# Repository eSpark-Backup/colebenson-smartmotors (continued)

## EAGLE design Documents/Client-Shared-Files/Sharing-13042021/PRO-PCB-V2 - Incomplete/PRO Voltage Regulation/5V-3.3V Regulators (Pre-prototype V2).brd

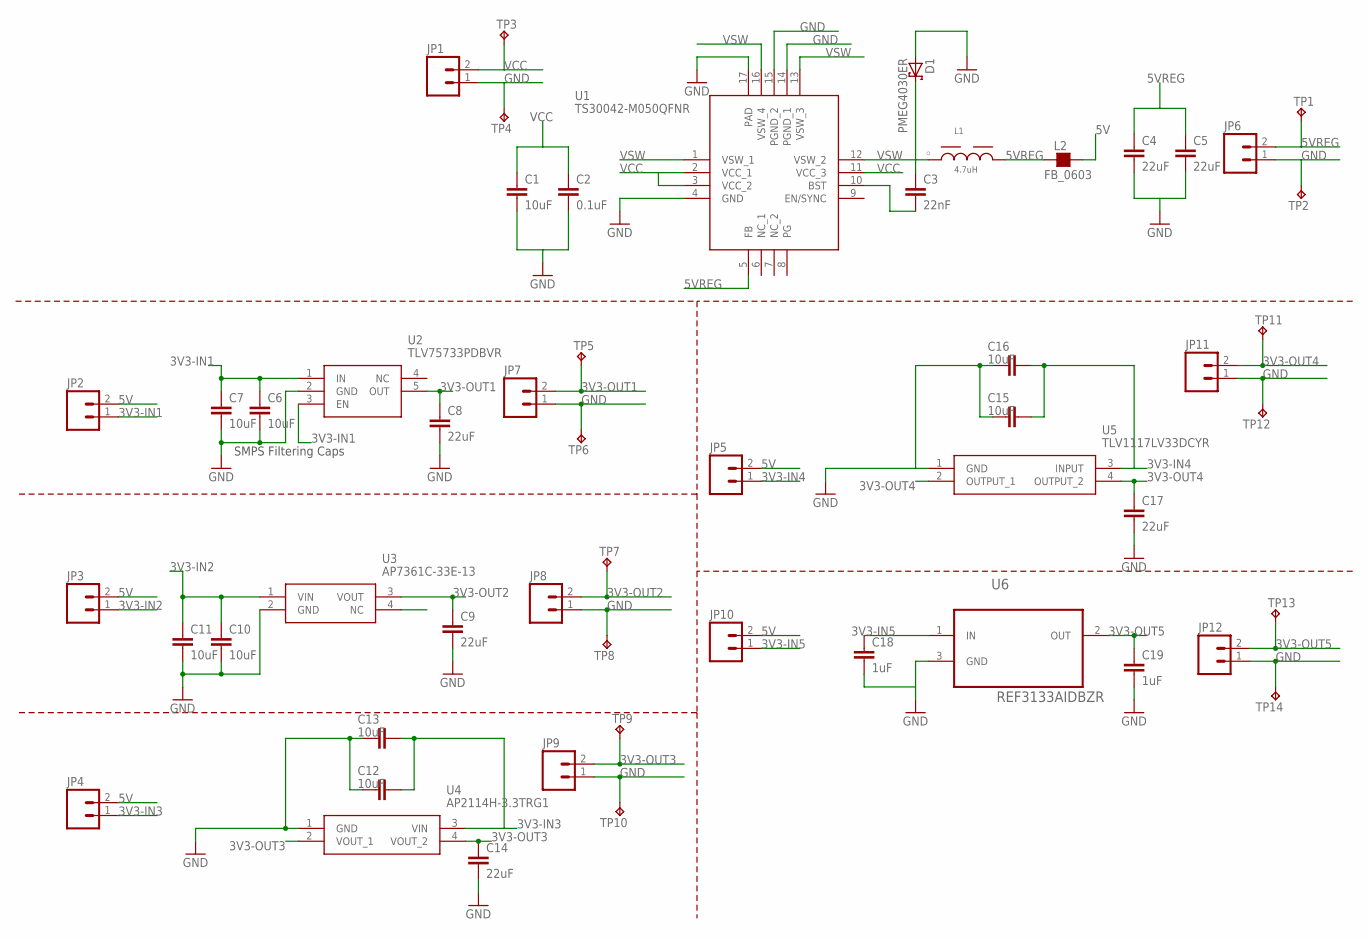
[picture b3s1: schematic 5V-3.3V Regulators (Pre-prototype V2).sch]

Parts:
C1: 10uF; 1206
C2: 0.1uF; 0603-CAP
C3: 22nF; 0402-CAP
C4, C5, C8, C9, C14, C17: 22uF; 0805
C6, C7, C10, C11, C12, C13, C15, C16: 10uF; 0805
C18, C19: 1uF; 0805
D1: PMEG4030ER; SOD123W
JP1, JP2, JP3, JP4, JP5, JP6, JP7, JP8, JP9, JP10, JP11, JP12: M02PTH; 1X02
L1: 4.7uH; WE-PD2_5848/5820
L2: FB_0603; L0603
TP1, TP2, TP3, TP4, TP5, TP6, TP7, TP8, TP9, TP10, TP11, TP12, TP13, TP14: TP-040
U1: TS30042-M050QFNR; QFN16
U2: TLV75733PDBVR; SOT95P280X145-5N
U3: AP7361C-33E-13; SOT230P700X165-4N
U4: AP2114H-3.3TRG1; SOT230P700X180-4N
U5: TLV1117LV33DCYR; SOT230P700X180-4N
U6: REF3133AIDBZR; SOT95P237X112-3N

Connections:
3V3-IN1: C6.1, C7.1, JP2.1, U2.1 (IN), U2.3 (EN)
3V3-IN2: C10.1, C11.1, JP3.1, U3.1 (VIN)
3V3-IN3: C12.1, C13.1, JP4.1, U4.3 (VIN)
3V3-IN4: C15.1, C16.1, JP5.1, U5.3 (INPUT)
3V3-IN5: C18.1, JP10.1, U6.1 (IN)
3V3-OUT1: C8.1, JP7.2, TP5.1, U2.5 (OUT)
3V3-OUT2: C9.1, JP8.2, TP7.1, U3.3 (VOUT)
3V3-OUT3: C14.1, JP9.2, TP9.1, U4.2 (VOUT_1), U4.4 (VOUT_2)
3V3-OUT4: C17.1, JP11.2, TP11.1, U5.2 (OUTPUT_1), U5.4 (OUTPUT_2)
3V3-OUT5: C19.1, JP12.2, TP13.1, U6.2 (OUT)
5V: JP2.2, JP3.2, JP4.2, JP5.2, JP10.2, L2.2
5VREG: C4.1, C5.1, JP6.2, L1.2, L2.1, TP1.1, U1.5 (FB)
GND: C1.2, C2.2, C4.2, C5.2, C6.2, C7.2, C8.2, C9.2, C10.2, C11.2, C12.2, C13.2, C14.2, C15.2, C16.2, C17.2, C18.2, C19.2, D1.2 (A), JP1.1, JP6.1, JP7.1, JP8.1, JP9.1, JP11.1, JP12.1, TP2.1, TP4.1, TP6.1, TP8.1, TP10.1, TP12.1, TP14.1, U1.4 (GND), U1.14 (PGND_1), U1.15 (PGND_2), U1.17 (PAD), U2.2 (GND), U3.2 (GND), U4.1 (GND), U5.1 (GND), U6.3 (GND)
unnamed: C3.2, U1.10 (BST)
VCC: C1.1, C2.1, JP1.2, TP3.1, U1.2 (VCC_1), U1.3 (VCC_2), U1.11 (VCC_3)
VSW: C3.1, D1.1 (K), L1.1, U1.1 (VSW_1), U1.12 (VSW_2), U1.13 (VSW_3), U1.16 (VSW_4)

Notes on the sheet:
SMPS Filtering Caps

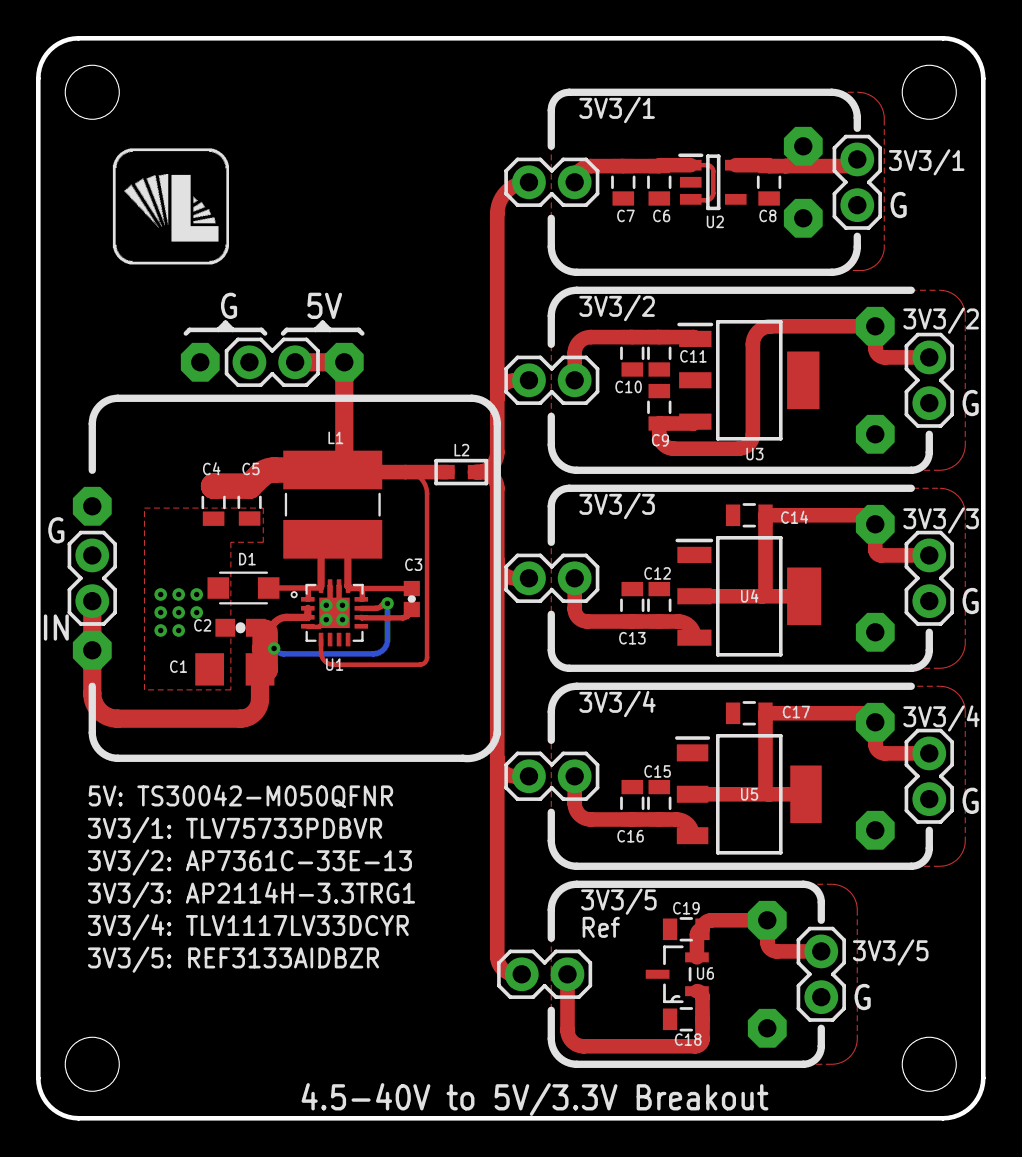
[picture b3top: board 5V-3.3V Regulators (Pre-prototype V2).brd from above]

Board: 2 copper layers, 52.5 x 60.0 mm, 54 parts (0 on the bottom side), 16 nets.

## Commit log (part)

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2022-01-08 All changes in #35. PCB updated.
2022-01-10 Routing in Top PCB.
2022-01-28 Power section updated #39
2022-01-29 #40 Completed
2022-01-29 Power section changed in top board #41. PDF creataed.
2022-01-31 Power section completed #41. Fresh PDF generated.
2022-02-01 3.3V LED added. Fresh PDF generated. Refer to #45 for details
    All required connections updated.
2022-02-01 22uH inductor replaced in Power section #44
2022-02-02 #42 Completed
2022-02-05 Encoder Noise Charts uploaded
2022-02-07 Ferrite beads added in schematic and library issue #48
2022-02-10 #51 Completed
2022-02-11 #50 and #52 updated.
2022-02-12 issue #50 and #52 completed
2022-02-14 #54 Completed
2022-02-15 #54 Error removed
2022-02-15 #55 Completed
2022-02-16 library compiled to avoid conflict while merging library addition branch,
2022-02-17 Regulator outputs updated, isolated coverter completed, gnds separated in all sheets.
2022-02-17 #58 Completed @UroojNav Inductor b add kr dia ha Acc to #55
2022-02-18 Changes done acc #47
2022-02-21 Parts Placement acc: #60
2022-02-22 GNDs isolated, signals corrected and errors removed #47
2022-02-22 Generated step files of Top board
2022-02-24 Corrections of isolated signals #58 #47
2022-02-24 Replaced switches with headers Issue #64
2022-02-24 PCB Routing completed #62 (errors and Warning remains)
2022-02-26 Minor changes in PCB. Refer to #70
2022-02-26 Changes done acc: #71
2022-02-28 Changes done acc #74
2022-02-28 Issue #75 Pending
2022-02-28 Minor changes in SM_Bottom_PCB after review. Refer to #73 PCB Designing -Review of routing of SM_Bottom_PCB #73
2022-03-03 Changes done according to #77
2022-03-03 Design PDFs generated (both boards)
2022-03-05 History and Preview folders deleted after Review of Both PCB's.
2022-03-07 Deliverables generated(Pick and place file and step file remaining
2022-03-11 Top Board Schematic Review (Pending)
2022-03-14 MAX14850ASE+ lib corrected. #81 resolved.
2022-03-14 #80 resolved.
2022-03-15 J1 replaced #83 PCB updated.
2022-03-16 #31 Completed.
2022-03-16 Revert "#31 Completed."
    This reverts commit dc2824ba49c5024c31e5d71a851132d0e0f728fc.
2022-03-18 #89 Completed
2022-03-21 Changes done acc #91 and Fresh deliverables generated #85
2022-03-22 Changes done acc #92(incompleted)
2022-03-25 #92 Completed
2022-03-28 #95 Completed
2022-03-29 Alternate added for ESD diodes and X2 #95
2022-03-31 PCB Updated acc to #98 and deliverables generated (#85) for top board
2022-04-01 Top Sheet Reviewed
2022-04-01 Revert "Schematic review"
2022-04-01 #104 Completed
2022-04-02 U4 changed in bottom board. #103
2022-04-06 #105 Completed
2022-04-06 Fresh Deliverables generated for bottom board and PDF generated for both board #106
2022-04-06 18ebcbc7 - Fresh DXF, DWG, 3D PDF and Step file for both Top and Bottom Boards generated.file.
2022-04-07 #107 Complete
2022-04-07 Mechanical Issues from client
2022-04-13 Worked completed on #109 and Fresh Deliverables generated
2022-04-27 Latest Deliverables generated for both Top and Bottom Boards.
2022-04-29 NC_Drill and Gerber Files Generated for Both both board
2022-07-19 #116 Completed
2022-07-21 branch info updated in readme of main
2022-07-21 modified .gitignore
2022-07-22 Word document submitted to client #121
2022-07-22 designator issue resolved #122
2022-07-22 connections corrected #125
2022-07-22 Resolved #123
2022-08-05 #128 #125 completed
2022-08-05 #130 Completed.
2022-08-05 Minor changes in Client BOM
2022-08-10 worked on #133 completed
2022-08-11 DRC Errors corrected #132 for details.
2022-08-12 BOM Economization #135
2022-08-15 @faizi968 TOP BOM Updated.
2022-08-15 BOM Economization (Complete) #135
2022-08-17 30-12V Buck Converter Design changes
2022-08-18 BOM and schematic changes #135
2022-08-19 #137 Updated Library,
2022-08-19 Library - Ref BOM - Schematic Changes #135 #137
2022-08-20 Top board BOM review (in progress)
2022-08-21 220nF capacitor part number merged
2022-08-21 Top Board BOM finalized
2022-08-21 Minor BOM formatting
2022-08-21 Bottom Board BOM Economization #135 (in progress)
2022-08-21 File name edited for BOMs (Top and Bottom)
2022-08-24 Routing completed of top board #138
2022-08-24 #139 Completed.
2022-08-24 added Evaluatioon-TLE5012B info to readme
2022-08-24 Removed .intlib
2022-08-24 BOM changes after schematic redesign
2022-08-24 LED Glass pipe link added
2022-08-24 Minor BOM correction
2022-08-25 Bottom board completed #141
2022-08-26 Review done #141 .
2022-08-31 Updated top board and deliverables.
2022-09-06 Design Files and Deliverables copied from Evaluation Branch.
2022-09-07 J11 added to Top board BOM
2022-09-21 Supplier BOM (20_TopBoards) complete
2022-09-21 Supplier BOM preparation
2022-09-21 BOM formatting
2022-09-22 LSM6DSL added to schematic #151
2022-09-22 Changes in PCB done #151 for details.
2022-11-11 #152 Capacitor C1 Updated In PCB and Deliverables Generated.
2023-01-04 #153 Done.
2023-01-04 #155 Done.
2023-01-04 Deliverables shared with client
2023-01-25 removed extra files
2023-01-26 Changes in bottom sheet #157
2023-01-26 pdfs generated for top and bottom projects
2023-01-27 #158 In-progress.
2023-01-30 #159 Bottom Board BOM Updated
2023-02-01 #159 Updated Files
2023-02-15 #158 Fresh deliverables generated for Top Board
2023-05-05 filter caps changed #160
2023-05-05 sense resistor value changed #160
2023-05-08 #160 Routing Completed No DRC error.
2023-05-08 #161 Done. Fresh deliverables generated.
2023-05-10 #160 2.2nf Cap and 50mR resistor added in BOM
2023-05-29 step files of PCB #161
2023-05-30 #161 Fresh deliverables generated.
2023-05-30 Gerber's, Pick n Place and BOM folders moved to Design Files from Deliverables folder.
2023-06-12 Connectors J2, J5 changed in schematic: #160 In-Progress.
2023-06-20 XT60 connector added
2023-06-21 #160 Ethernet connector - Solder Bridges removed - Motor Connector changed - Boot header changed
2023-06-23 Library parts added
2023-06-26 #160 Changes in Bottom Board for SB1 and U6.
2023-06-28 #160 Done for Bottom Board: U4, U6 and Connector Cutout updated.
2023-07-03 #160 Changes in Top and Bottom Board PCB for P1, P2, J2 and J5.
2023-07-05 #160 In-progress: Changes in Top Board for Diodes D4, D5, D7, D10 and R14, R16.
2023-07-06 #18 CRS01(TE85L,Q,M) Diode footprint edited
2023-07-06 #18 in eSpark Hardware Switches Added
2023-07-06 #18 B4P-VH-FB-B(LF)(SN) 3d Model Added
2023-07-06 #160 SW1 Corrections remaining.
2023-07-06 #160 Done: SW1 and 5V LED moved to new location.
2023-07-07 #160 Done: Corrections in Routing of Top Board done: Old Gerbsers and Pick n Place files deleted for Top and Bottom Board.
2023-07-16 #160 Corrections for Stepper and XT60 connectors done: Corrections for Boot Header remaining.
2023-07-17 #18 JST Connector added
2023-07-17 #160 J6 Updated in both schematic and PCB.
2023-07-17 #160 Footprint updated in Top Board PCB after 3D body update
2023-07-18 #162 U10 Footprint Edited
2023-07-20 changes updated in PCB as mention in #160 for top board And D1 removed from PCB in Bottom Board
2023-07-20 #160 Minor corrections in Routing: Un-tented Via's are tented now in Bottom Board PCB.
2023-07-21 #160 Designators and Text size edited and Fills added for GND.
2023-07-21 #160 BOM Update completed
2023-07-21 #160 Latest 3D Renderings and Step file of both Top and Bottom Boards created.
2023-07-24 #160 Latest Step file generated: Corrections in Routing.
2023-07-27 #67 Switch and JST added
2023-07-27 Design version numbers added
2023-07-27 Schematic doc added and renamed #163
2023-07-31 #163 PCB Design Sub_Board
    PCB Design Sub_Board
2023-08-02 #163 Flipped Connections
    Flipped Connections
2023-08-02 #163 PCB reviewed and changes done accordingly, Deliverables generated
2023-08-02 #163 BOM Completed.
2023-08-03 #163 Fresh Deliverables of Sub Board created: Folders name corrected.
2023-08-03 Bottom Board BOM updated #160
2023-09-21 #164 JST and Capacitor added
2023-09-21 #164 Done for PT100 and C49.
2023-09-22 Top BOard BOM CHanges Completed.
2023-11-16 Button schematic pin corrected.
2023-11-22 #167 Rotary Encoder IC's symbol added "AEAT-9955"
2023-11-22 #167 Pin 33 added for AEAT-9955
2023-11-22 #167 TS2940CW33 RPG Added in Library
2023-11-23 #167 New Regulator and Encoder ICs Added
2023-11-23 #167 Updated Part Added
2023-11-23 #167 Files and Folders renamed to v3.4
2023-11-24 #167 30mil Test Point added
2023-11-24 #167 In-progress for Top Board PCB.
2023-11-27 #167 Resistor , cap and Inductor added
2023-11-28 #167 Inductor added
2023-11-28 #167 Newest Regulator IC added
2023-11-28 #167 inductor 3d Model added
2023-11-29 #167 Modifications in Routing: Fresh Deliverables generated for Top-Board-v3.4.
2023-12-08 #167 Changes in Split planes on Top Board-v3.4.
2023-12-13 #167 Changes in Routing for Split planes.
2023-12-14 #168 ISO7740FDBQR, ISO6762FQDWRQ1 ICs added.
2023-12-18 #167 Changes In-progress.
2023-12-19 #167 Routing In-progress.
2023-12-21 7 Routes remaining( placement of D19 is remaining)
2023-12-21 #168 D20,D21 Schematic Symbol Updated.
2023-12-21 #168 U4 Footprint Edited Bottom Board
2023-12-22 #167 top board Routing completed and Deliverables generated for bottom Board
2023-12-24 #167 Fresh Deliverables after New Layerstackup.
2023-12-24 #167 Updated Gerbers.
2023-12-26 #169 IC And resistor added
2023-12-27 #169 Mosfet Added
2023-12-27 #167 Soft Start Circuit added
2023-12-29 #167 Changes in Routing of both Top and Bottom Boards-v3.4.:
2024-01-04 #167 Routing updated in Bottom Board-v3.4.
2024-01-05 #167 Top Board BOM Updated
2024-01-05 #167 TOP and Bottom Board eSpark BOM Updated.
2024-01-10 #167 Changes in Schematics done and changes in PCB remaining for Encoder and PT100 Sensor:
2024-01-11 #169 Header [1.25-2PWB] added.
2024-01-12 #169 Connector overlay edited.
2024-01-15 #167 Changes in Schematic and PCB of Bottom Board PCB.
2024-01-15 #167 Fresh Step file added in relevant folders for both Top and Bottom Board PCB-v3.4.
2024-01-15 Bottom board LED1 removed #167
2024-01-16 #167 Corrections in Top and Bottom Board PCBs: Old Deliverables deleted.
2024-01-16 #167 Fresh Renderings and step files of all three boards generated.
2024-01-16 #167 Gerbers, Pick n Place and Assembly Drawings generated for Sub Board. for Top and Bottom Board PCB's.
2024-01-16 #167 BOM, Gerbers, Pick n Place and Assembly Drawings generated for Top Board-v3.4.
2024-01-17 #167 Fresh Deliverables of Sub_Board Generated.
2024-01-17 #167 Fresh Deliverables of Bottom Board generated.
2024-01-17 #169 Diode added
2024-01-17 Revert "#167 Diode for reverse polarity protection added"
    This reverts commit 96902cf09be724120534b2d72a66501fe64f0aa7.
2024-01-17 #167 Updated Deliverables after Notes Section deletion.
2024-01-22 #167 Encoder connections changed to SPI3 on schematic
2024-01-23 #167 Top Board Client BOM missing Part no Added
2024-01-23 #167 Sub Board Client BOM edited.
2024-01-26 #167 Fresh Gerbers and NC Drill File generated for Bottom Board-v3.4 after layer stackup adjustments.
2024-01-29 #167 Latest step files of Top and Bottom Boards-v3.4 created.
2024-05-02 Branch v3.4 manual merge into main branch (prod release)
2024-05-02 #174 C22 changed to 189RV0038
2024-05-02 #174 C22 Update in Client BOM.
2024-06-05 Files renamed
2024-06-05 @basit-eSpark Diodes added
2024-06-05 #174 Above multiple changes done
2024-06-05 @basit-eSpark Zener Diode added
2024-06-05 #174 Changes in PCB In-progress.
2024-06-06 #174 Q5 Updated to DPAK. Found one suitable MOSFET
2024-06-06 #174 Client BOM Updated.
2024-06-07 v3.5 pdf generated
2024-06-13 netlabel changed from 30VDC to 36VDC
2024-06-13 #174 BOM highlights edite
2024-06-21 File and folder modification v3.4
2024-06-21 Library folder version added
